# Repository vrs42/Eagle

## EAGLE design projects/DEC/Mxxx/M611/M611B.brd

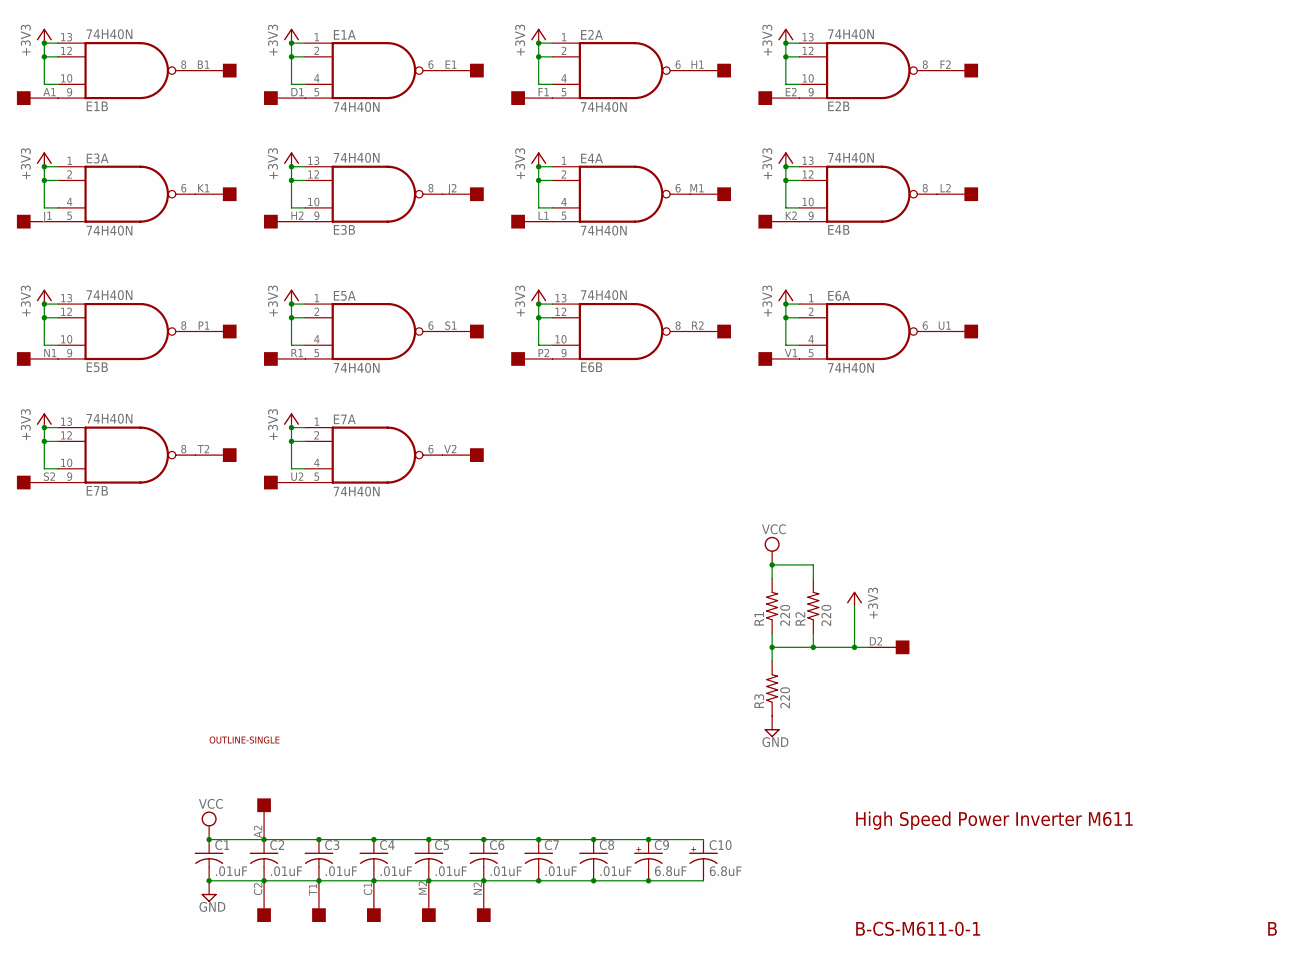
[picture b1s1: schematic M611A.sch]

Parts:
C1, C2, C3, C4, C5, C6, C7, C8: .01uF; C050-025X075
C9, C10: 6.8uF; E12-8
E1, E2, E3, E4, E5, E6, E7: 74H40N; DIL14
R1, R2, R3: 220; 0207/10
U$1: SINGLE; EDGE-CON2
U$4: OUTLINE-SINGLE; SINGLE

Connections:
+3V3: E1.1 (I0), E1.2 (I1), E1.4 (I2), E1.10 (I1), E1.12 (I2), E1.13 (I3), E2.1 (I0), E2.2 (I1), E2.4 (I2), E2.10 (I1), E2.12 (I2), E2.13 (I3), E3.1 (I0), E3.2 (I1), E3.4 (I2), E3.10 (I1), E3.12 (I2), E3.13 (I3), E4.1 (I0), E4.2 (I1), E4.4 (I2), E4.10 (I1), E4.12 (I2), E4.13 (I3), E5.1 (I0), E5.2 (I1), E5.4 (I2), E5.10 (I1), E5.12 (I2), E5.13 (I3), E6.1 (I0), E6.2 (I1), E6.4 (I2), E6.10 (I1), E6.12 (I2), E6.13 (I3), E7.1 (I0), E7.2 (I1), E7.4 (I2), E7.10 (I1), E7.12 (I2), E7.13 (I3), R1.1, R2.1, R3.2, U$1.D2
GND: C1.2, C2.2, C3.2, C4.2, C5.2, C6.2, C7.2, C8.2, C9.-, C10.-, E1.7 (GND), E2.7 (GND), E3.7 (GND), E4.7 (GND), E5.7 (GND), E6.7 (GND), E7.7 (GND), R3.1, U$1.C1, U$1.C2, U$1.M2, U$1.N2, U$1.T1
unnamed: E1.9 (I0), U$1.A1
unnamed: E1.8 (O), U$1.B1
unnamed: E1.5 (I3), U$1.D1
unnamed: E1.6 (O), U$1.E1
unnamed: E2.6 (O), U$1.H1
unnamed: E2.5 (I3), U$1.F1
unnamed: E3.5 (I3), U$1.J1
unnamed: E3.6 (O), U$1.K1
unnamed: E2.9 (I0), U$1.E2
unnamed: E2.8 (O), U$1.F2
unnamed: E3.9 (I0), U$1.H2
unnamed: E3.8 (O), U$1.J2
unnamed: E4.5 (I3), U$1.L1
unnamed: E4.6 (O), U$1.M1
unnamed: E4.9 (I0), U$1.K2
unnamed: E4.8 (O), U$1.L2
unnamed: E5.9 (I0), U$1.N1
unnamed: E5.8 (O), U$1.P1
unnamed: E5.5 (I3), U$1.R1
unnamed: E5.6 (O), U$1.S1
unnamed: E6.9 (I0), U$1.P2
unnamed: E6.8 (O), U$1.R2
unnamed: E6.5 (I3), U$1.V1
unnamed: E6.6 (O), U$1.U1
unnamed: E7.9 (I0), U$1.S2
unnamed: E7.8 (O), U$1.T2
unnamed: E7.5 (I3), U$1.U2
unnamed: E7.6 (O), U$1.V2
VCC: C1.1, C2.1, C3.1, C4.1, C5.1, C6.1, C7.1, C8.1, C9.+, C10.+, E1.14 (VCC), E2.14 (VCC), E3.14 (VCC), E4.14 (VCC), E5.14 (VCC), E6.14 (VCC), E7.14 (VCC), R1.2, R2.2, U$1.A2

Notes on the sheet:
High Speed Power Inverter M611
B-CS-M611-0-1

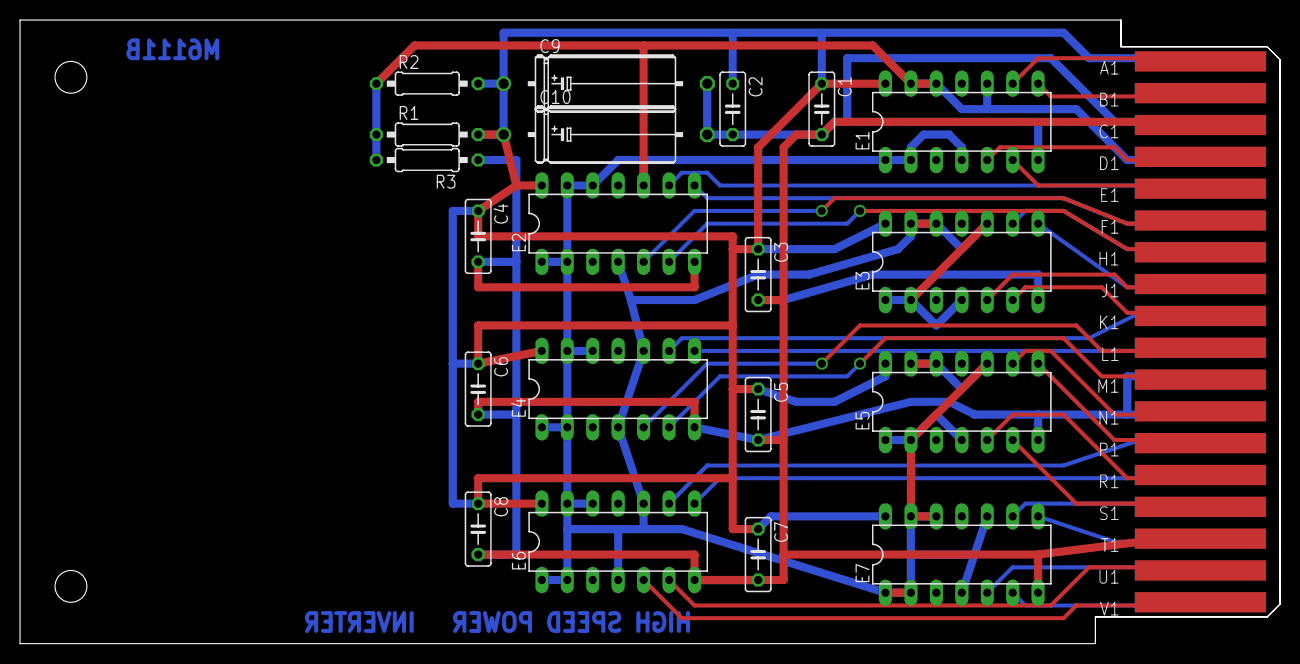
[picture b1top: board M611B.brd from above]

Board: 2 copper layers, 125.7 x 62.2 mm, 22 parts (0 on the bottom side), 31 nets.

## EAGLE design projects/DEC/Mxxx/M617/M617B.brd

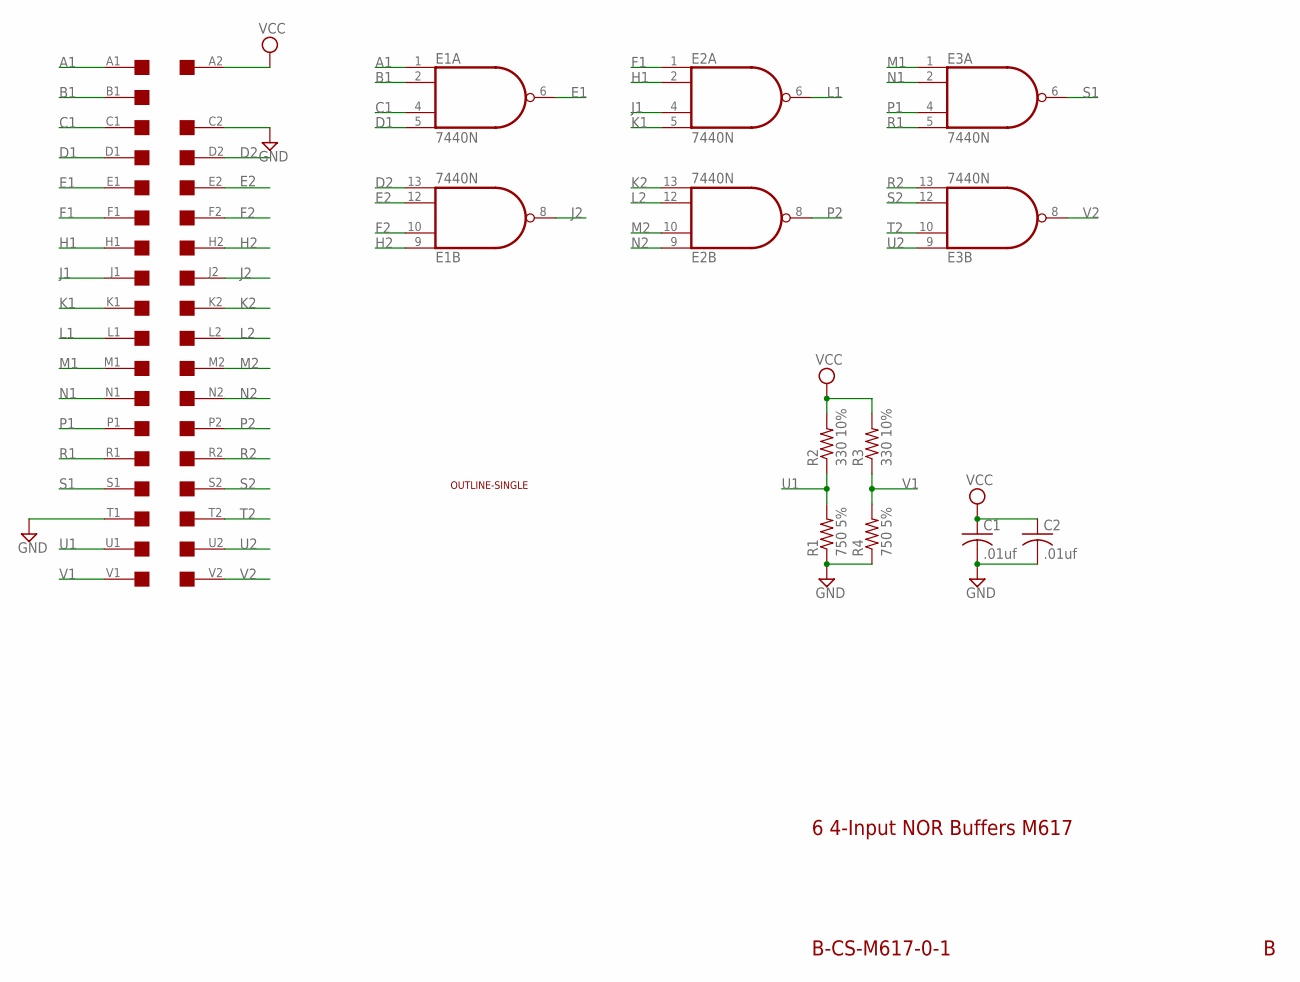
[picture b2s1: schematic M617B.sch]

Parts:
C1, C2: .01uf; C075-032X103
E1, E2, E3: 7440N; DIL14
R1, R4: 750 5%; 0207/15
R2, R3: 330 10%; 0207/15
U$1: SINGLE; EDGE-CON2
U$4: OUTLINE-SINGLE; SINGLE

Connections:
A1: E1.1 (I0), U$1.A1
B1: E1.2 (I1), U$1.B1
C1: E1.4 (I2), U$1.C1
D1: E1.5 (I3), U$1.D1
D2: E1.13 (I3), U$1.D2
E1: E1.6 (O), U$1.E1
E2: E1.12 (I2), U$1.E2
F1: E2.1 (I0), U$1.F1
F2: E1.10 (I1), U$1.F2
GND: C1.2, C2.2, E1.7 (GND), E2.7 (GND), E3.7 (GND), R1.1, R4.1, U$1.C2, U$1.T1
H1: E2.2 (I1), U$1.H1
H2: E1.9 (I0), U$1.H2
J1: E2.4 (I2), U$1.J1
J2: E1.8 (O), U$1.J2
K1: E2.5 (I3), U$1.K1
K2: E2.13 (I3), U$1.K2
L1: E2.6 (O), U$1.L1
L2: E2.12 (I2), U$1.L2
M1: E3.1 (I0), U$1.M1
M2: E2.10 (I1), U$1.M2
N1: E3.2 (I1), U$1.N1
N2: E2.9 (I0), U$1.N2
P1: E3.4 (I2), U$1.P1
P2: E2.8 (O), U$1.P2
R1: E3.5 (I3), U$1.R1
R2: E3.13 (I3), U$1.R2
S1: E3.6 (O), U$1.S1
S2: E3.12 (I2), U$1.S2
T2: E3.10 (I1), U$1.T2
U1: R1.2, R2.1, U$1.U1
U2: E3.9 (I0), U$1.U2
V1: R3.1, R4.2, U$1.V1
V2: E3.8 (O), U$1.V2
VCC: C1.1, C2.1, E1.14 (VCC), E2.14 (VCC), E3.14 (VCC), R2.2, R3.2, U$1.A2

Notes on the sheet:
6 4-Input NOR Buffers M617
B-CS-M617-0-1

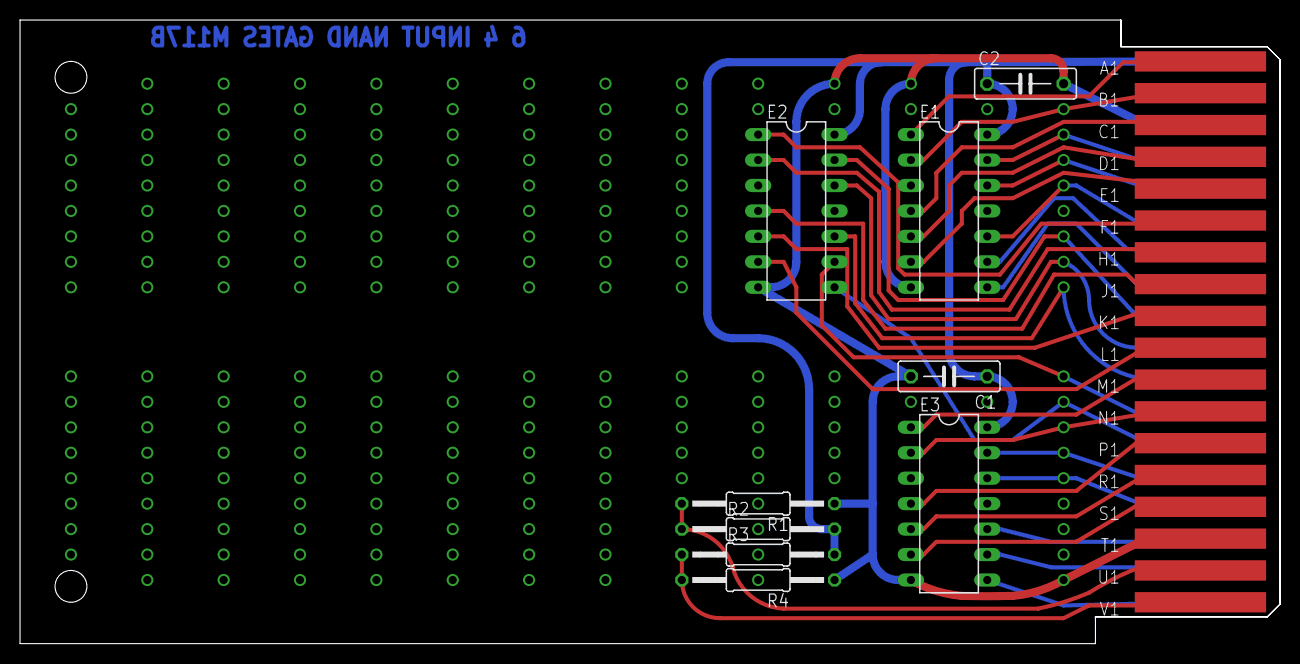
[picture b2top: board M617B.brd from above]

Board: 2 copper layers, 125.7 x 62.2 mm, 11 parts (0 on the bottom side), 34 nets.

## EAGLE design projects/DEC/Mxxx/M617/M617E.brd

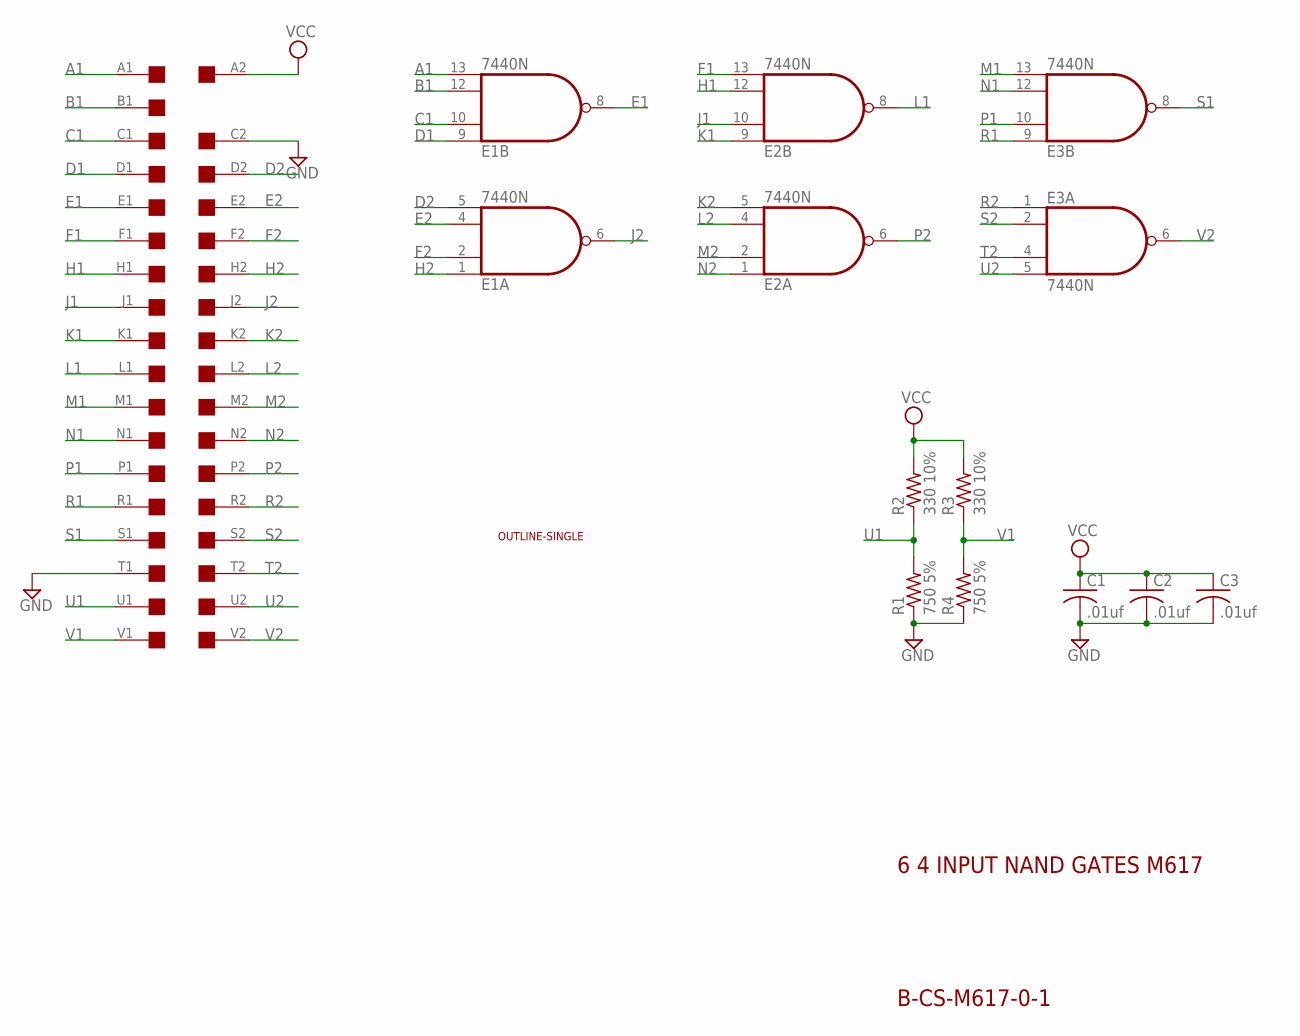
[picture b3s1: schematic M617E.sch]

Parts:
C1, C2, C3: .01uf; C050-025X075
E1, E2, E3: 7440N; DIL14
R1, R4: 750 5%; 0207/10
R2, R3: 330 10%; 0207/10
U$1: SINGLE; EDGE-CON2
U$4: OUTLINE-SINGLE; SINGLE

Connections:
A1: E1.13 (I3), U$1.A1
B1: E1.12 (I2), U$1.B1
C1: E1.10 (I1), U$1.C1
D1: E1.9 (I0), U$1.D1
D2: E1.5 (I3), U$1.D2
E1: E1.8 (O), U$1.E1
E2: E1.4 (I2), U$1.E2
F1: E2.13 (I3), U$1.F1
F2: E1.2 (I1), U$1.F2
GND: C1.2, C2.2, C3.2, E1.7 (GND), E2.7 (GND), E3.7 (GND), R1.1, R4.1, U$1.C2, U$1.T1
H1: E2.12 (I2), U$1.H1
H2: E1.1 (I0), U$1.H2
J1: E2.10 (I1), U$1.J1
J2: E1.6 (O), U$1.J2
K1: E2.9 (I0), U$1.K1
K2: E2.5 (I3), U$1.K2
L1: E2.8 (O), U$1.L1
L2: E2.4 (I2), U$1.L2
M1: E3.13 (I3), U$1.M1
M2: E2.2 (I1), U$1.M2
N1: E3.12 (I2), U$1.N1
N2: E2.1 (I0), U$1.N2
P1: E3.10 (I1), U$1.P1
P2: E2.6 (O), U$1.P2
R1: E3.9 (I0), U$1.R1
R2: E3.1 (I0), U$1.R2
S1: E3.8 (O), U$1.S1
S2: E3.2 (I1), U$1.S2
T2: E3.4 (I2), U$1.T2
U1: R1.2, R2.1, U$1.U1
U2: E3.5 (I3), U$1.U2
V1: R3.1, R4.2, U$1.V1
V2: E3.6 (O), U$1.V2
VCC: C1.1, C2.1, C3.1, E1.14 (VCC), E2.14 (VCC), E3.14 (VCC), R2.2, R3.2, U$1.A2

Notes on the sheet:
6 4 INPUT NAND GATES M617
B-CS-M617-0-1

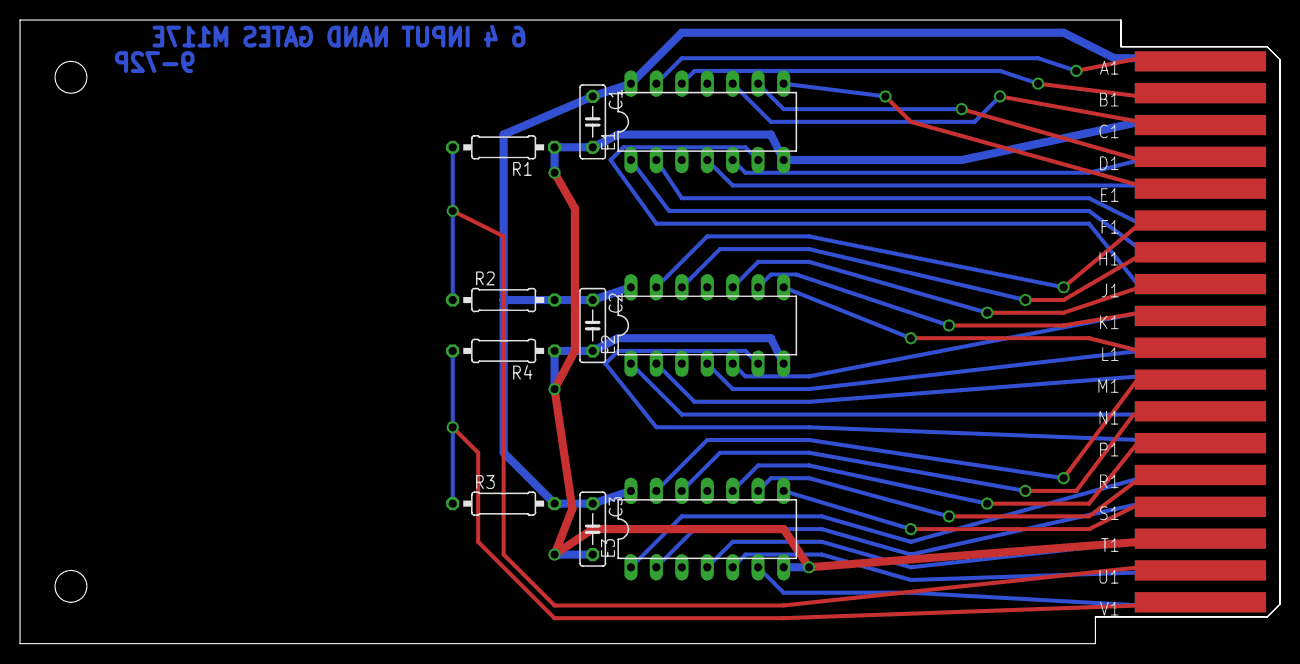
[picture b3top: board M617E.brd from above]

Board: 2 copper layers, 125.7 x 62.2 mm, 12 parts (0 on the bottom side), 34 nets.

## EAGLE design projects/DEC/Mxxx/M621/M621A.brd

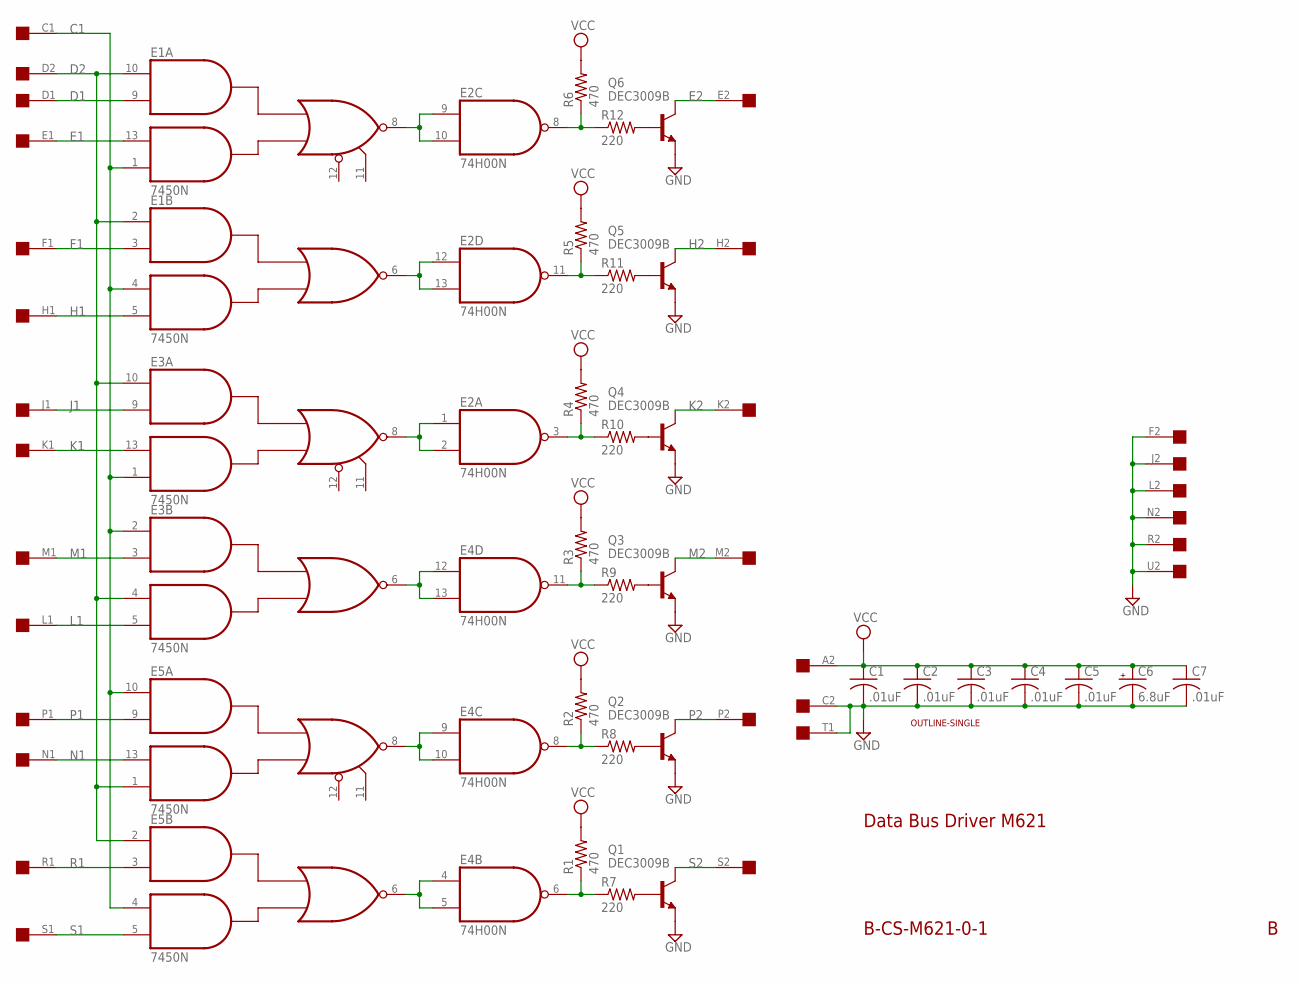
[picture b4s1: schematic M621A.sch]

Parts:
C1, C2, C3, C4, C5, C7: .01uF; C063-025X075
C6: 6.8uF; E15-5
E1, E3, E5: 7450N; DIL14
E2, E4: 74H00N; DIL14
Q1, Q2, Q3, Q4, Q5, Q6: DEC3009B; TO5
R1, R2, R3, R4, R5, R6: 470; 0207/10
R7, R8, R9, R10, R11, R12: 220; 0207/10
U$1: OUTLINE-SINGLE; SINGLE
U$2: edge; EDGE-CON2

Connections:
C1: E1.1 (I4), E1.4 (I3), E3.1 (I4), E3.2 (I1), E5.4 (I3), E5.10 (I1), U$2.C1
D1: E1.9 (I2), U$2.D1
D2: E1.2 (I1), E1.10 (I1), E3.4 (I3), E3.10 (I1), E5.1 (I4), E5.2 (I1), U$2.D2
E1: E1.13 (I3), U$2.E1
E2: Q6.3 (C), U$2.E2
F1: E1.3 (I2), U$2.F1
GND: C1.2, C2.2, C3.2, C4.2, C5.2, C6.-, C7.2, E1.7 (GND), E2.7 (GND), E3.7 (GND), E4.7 (GND), E5.7 (GND), Q1.1 (E), Q2.1 (E), Q3.1 (E), Q4.1 (E), Q5.1 (E), Q6.1 (E), U$2.C2, U$2.F2, U$2.J2, U$2.L2, U$2.N2, U$2.R2, U$2.T1, U$2.U2
H1: E1.5 (I4), U$2.H1
H2: Q5.3 (C), U$2.H2
J1: E3.9 (I2), U$2.J1
K1: E3.13 (I3), U$2.K1
K2: Q4.3 (C), U$2.K2
L1: E3.5 (I4), U$2.L1
M1: E3.3 (I2), U$2.M1
M2: Q3.3 (C), U$2.M2
N1: E5.13 (I3), U$2.N1
unnamed: E2.8 (O), R6.1, R12.1
unnamed: E2.11 (O), R5.1, R11.1
unnamed: E2.3 (O), R4.1, R10.1
unnamed: E4.11 (O), R3.1, R9.1
unnamed: E4.8 (O), R2.1, R8.1
unnamed: E4.6 (O), R1.1, R7.1
unnamed: Q1.2 (B), R7.2
unnamed: Q2.2 (B), R8.2
unnamed: Q3.2 (B), R9.2
unnamed: Q4.2 (B), R10.2
unnamed: Q5.2 (B), R11.2
unnamed: Q6.2 (B), R12.2
unnamed: E1.6 (O), E2.12 (I0), E2.13 (I1)
unnamed: E1.8 (O), E2.9 (I0), E2.10 (I1)
unnamed: E2.1 (I0), E2.2 (I1), E3.8 (O)
unnamed: E3.6 (O), E4.12 (I0), E4.13 (I1)
unnamed: E4.9 (I0), E4.10 (I1), E5.8 (O)
unnamed: E4.4 (I0), E4.5 (I1), E5.6 (O)
P1: E5.9 (I2), U$2.P1
P2: Q2.3 (C), U$2.P2
R1: E5.3 (I2), U$2.R1
S1: E5.5 (I4), U$2.S1
S2: Q1.3 (C), U$2.S2
VCC: C1.1, C2.1, C3.1, C4.1, C5.1, C6.+, C7.1, E1.14 (VCC), E2.14 (VCC), E3.14 (VCC), E4.14 (VCC), E5.14 (VCC), R1.2, R2.2, R3.2, R4.2, R5.2, R6.2, U$2.A2

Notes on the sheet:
Data Bus Driver M621
B-CS-M621-0-1

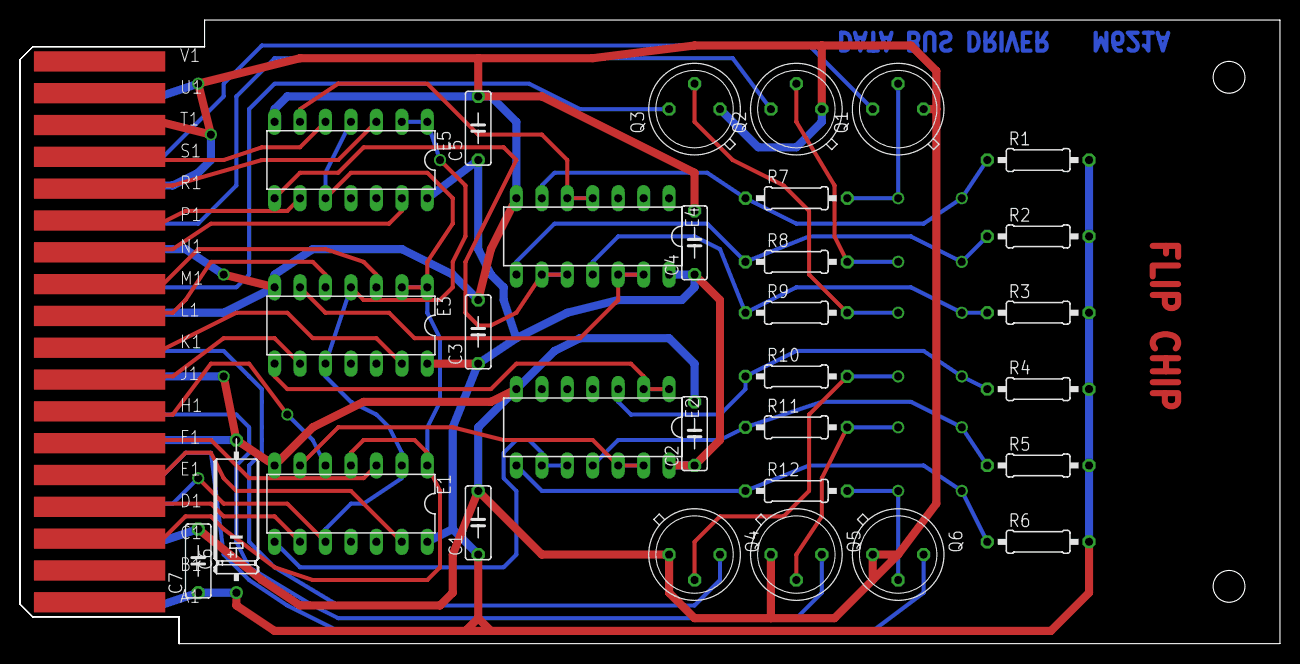
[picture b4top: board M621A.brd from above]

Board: 2 copper layers, 125.7 x 62.2 mm, 32 parts (0 on the bottom side), 40 nets.
